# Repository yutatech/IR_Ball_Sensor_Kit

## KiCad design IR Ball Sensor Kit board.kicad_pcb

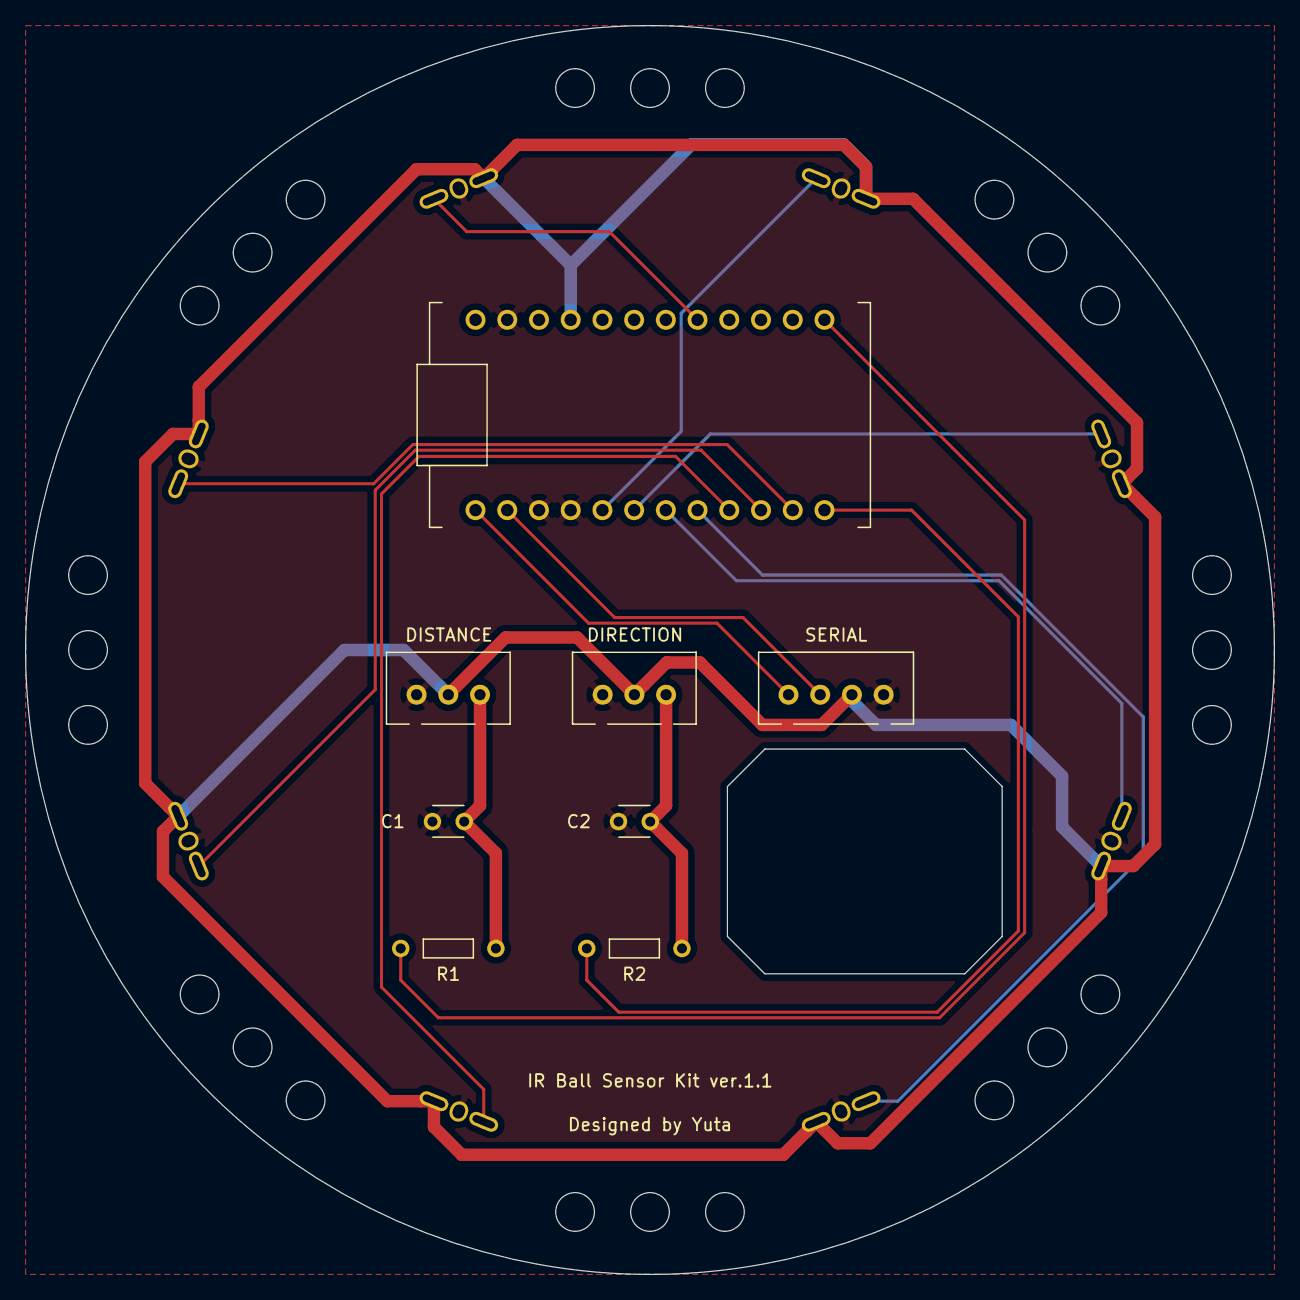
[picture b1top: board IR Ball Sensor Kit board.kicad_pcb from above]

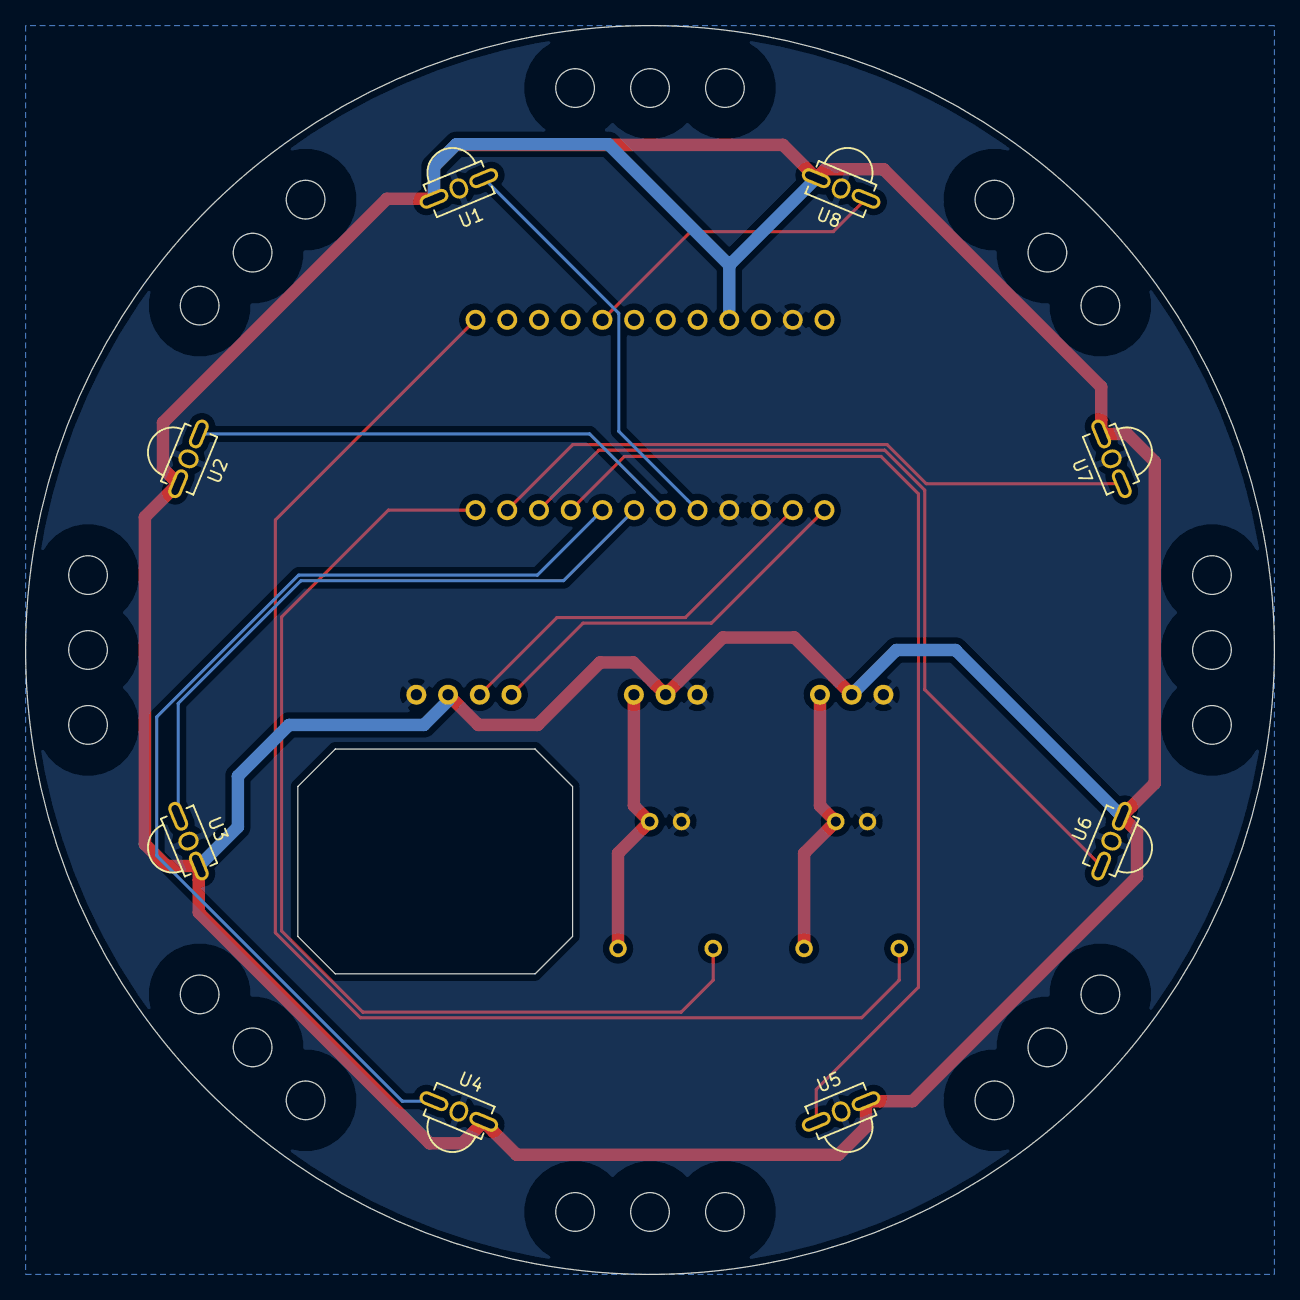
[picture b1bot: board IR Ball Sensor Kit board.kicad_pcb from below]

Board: 2 copper layers, 100.0 x 100.0 mm, 17 parts (8 on the bottom side), 16 nets.

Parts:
C1, C2: 0.1uF; 2pins
J1: l; CONN_01X12
J2: r; CONN_01X12
J3: DISTANCE; 3pins
J4: DIRECTION; 3pins
J5: SERIAL; 4pins
R1, R2: 47K; 2pins
U1, U2, U3, U4, U5, U6, U7, U8: TSSP58038

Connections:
+5V: J2.4, J3.2, J4.2, J5.3, U1.3, U2.3, U3.3, U4.3, U5.3, U6.3, U7.3, U8.3
/A0: J2.8, U8.1
/D2: J1.5, U1.1
/D3: J1.6, U2.1
/D4: J1.7, U3.1
/D5: J1.8, U4.1
/D6: J1.9, U5.1
/D7: J1.10, U6.1
/D8: J1.11, U7.1
/D9: J1.12, R2.2
/D10: J2.12, R1.2
/RX: J1.2, J5.2
/TX: J1.1, J5.1
GND: C1.2, C2.2, J1.3, J1.4, J2.2, J3.3, J4.3, J5.4, U1.2, U2.2, U3.2, U4.2, U5.2, U6.2, U7.2, U8.2
unnamed: C1.1, J3.1, R1.1
unnamed: C2.1, J4.1, R2.1

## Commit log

2022-09-10 add related files
2022-09-24 add manuals
